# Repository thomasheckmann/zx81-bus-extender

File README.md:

# zx81-bus-extender v1
ZX81 Expansion port extender with power LED. Simple :-)

KiCad 8 files availble, in case you want to play around with it yourself - or Gerber files for producing PCBs.

BOM for v1:
- [ ] 2 x Edge Connector for ZX81

-- And optional

- [ ] LED any color, SMD
- [ ] 1K Ohm resistor, SMD
- [ ] 100 nF capacitor, SMD

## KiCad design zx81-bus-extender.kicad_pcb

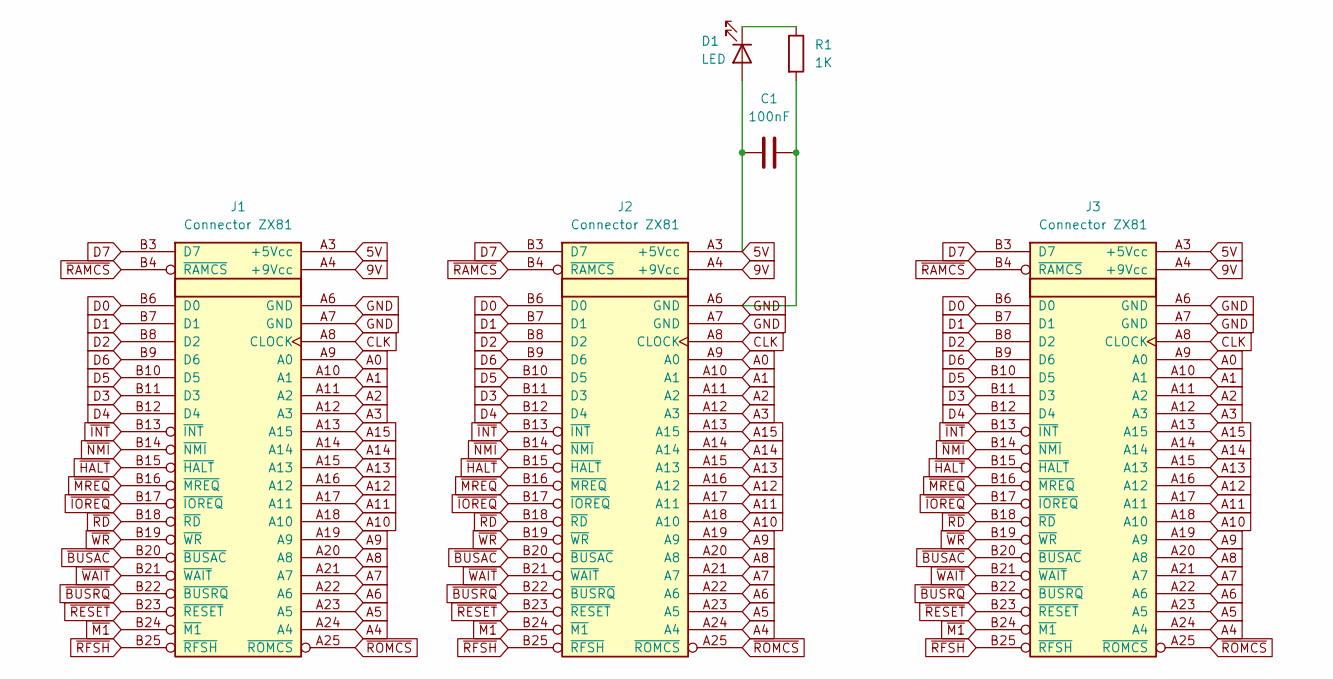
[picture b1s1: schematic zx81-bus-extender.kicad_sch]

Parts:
C1: 100nF; C_1206_3216Metric_Pad1.33x1.80mm_HandSolder
D1: LED; LED_1206_3216Metric_Pad1.42x1.75mm_HandSolder
J1: Connector ZX81; EDGE ZX81 BOTTOM
J2: Connector ZX81; EDGE ZX81 90
J3: Connector ZX81; EDGE ZX81 TOP
R1: 1K; R_1206_3216Metric_Pad1.30x1.75mm_HandSolder

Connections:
5V: C1.1, D1.2 (A), J1.A3 (+5Vcc), J2.A3 (+5Vcc), J3.A3 (+5Vcc)
9V: J1.A4 (+9Vcc), J2.A4 (+9Vcc), J3.A4 (+9Vcc)
A0: J1.A9 (A0), J2.A9 (A0), J3.A9 (A0)
A1: J1.A10 (A1), J2.A10 (A1), J3.A10 (A1)
A2: J1.A11 (A2), J2.A11 (A2), J3.A11 (A2)
A3: J1.A12 (A3), J2.A12 (A3), J3.A12 (A3)
A4: J1.A24 (A4), J2.A24 (A4), J3.A24 (A4)
A5: J1.A23 (A5), J2.A23 (A5), J3.A23 (A5)
A6: J1.A22 (A6), J2.A22 (A6), J3.A22 (A6)
A7: J1.A21 (A7), J2.A21 (A7), J3.A21 (A7)
A8: J1.A20 (A8), J2.A20 (A8), J3.A20 (A8)
A9: J1.A19 (A9), J2.A19 (A9), J3.A19 (A9)
A10: J1.A18 (A10), J2.A18 (A10), J3.A18 (A10)
A11: J1.A17 (A11), J2.A17 (A11), J3.A17 (A11)
A12: J1.A16 (A12), J2.A16 (A12), J3.A16 (A12)
A13: J1.A15 (A13), J2.A15 (A13), J3.A15 (A13)
A14: J1.A14, J2.A14, J3.A14
A15: J1.A13 (A15), J2.A13 (A15), J3.A13 (A15)
CLK: J1.A8 (CLOCK), J2.A8 (CLOCK), J3.A8 (CLOCK)
D0: J1.B6 (D0), J2.B6 (D0), J3.B6 (D0)
D1: J1.B7 (D1), J2.B7 (D1), J3.B7 (D1)
D2: J1.B8 (D2), J2.B8 (D2), J3.B8 (D2)
D3: J1.B11 (D3), J2.B11 (D3), J3.B11 (D3)
D4: J1.B12 (D4), J2.B12 (D4), J3.B12 (D4)
D5: J1.B10 (D5), J2.B10 (D5), J3.B10 (D5)
D6: J1.B9 (D6), J2.B9 (D6), J3.B9 (D6)
D7: J1.B3 (D7), J2.B3 (D7), J3.B3 (D7)
GND: C1.2, J1.A6 (GND), J1.A7 (GND), J2.A6 (GND), J2.A7 (GND), J3.A6 (GND), J3.A7 (GND), R1.2
unnamed: D1.1 (K), R1.1
~BUSAC: J1.B20 (~BUSAC), J2.B20 (~BUSAC), J3.B20 (~BUSAC)
~BUSRQ: J1.B22 (~BUSRQ), J2.B22 (~BUSRQ), J3.B22 (~BUSRQ)
~HALT: J1.B15 (~HALT), J2.B15 (~HALT), J3.B15 (~HALT)
~INT: J1.B13 (~INT), J2.B13 (~INT), J3.B13 (~INT)
~IOREQ: J1.B17 (~IOREQ), J2.B17 (~IOREQ), J3.B17 (~IOREQ)
~M1: J1.B24 (~M1), J2.B24 (~M1), J3.B24 (~M1)
~MREQ: J1.B16 (~MREQ), J2.B16 (~MREQ), J3.B16 (~MREQ)
~NMI: J1.B14 (~NMI), J2.B14 (~NMI), J3.B14 (~NMI)
~RAMCS: J1.B4 (~RAMCS), J2.B4 (~RAMCS), J3.B4 (~RAMCS)
~RD: J1.B18 (~RD), J2.B18 (~RD), J3.B18 (~RD)
~RESET: J1.B23 (~RESET), J2.B23 (~RESET), J3.B23 (~RESET)
~RFSH: J1.B25 (~RFSH), J2.B25 (~RFSH), J3.B25 (~RFSH)
~ROMCS: J1.A25 (~ROMCS), J2.A25 (~ROMCS), J3.A25 (~ROMCS)
~WAIT: J1.B21 (~WAIT), J2.B21 (~WAIT), J3.B21 (~WAIT)
~WR: J1.B19 (~WR), J2.B19 (~WR), J3.B19 (~WR)

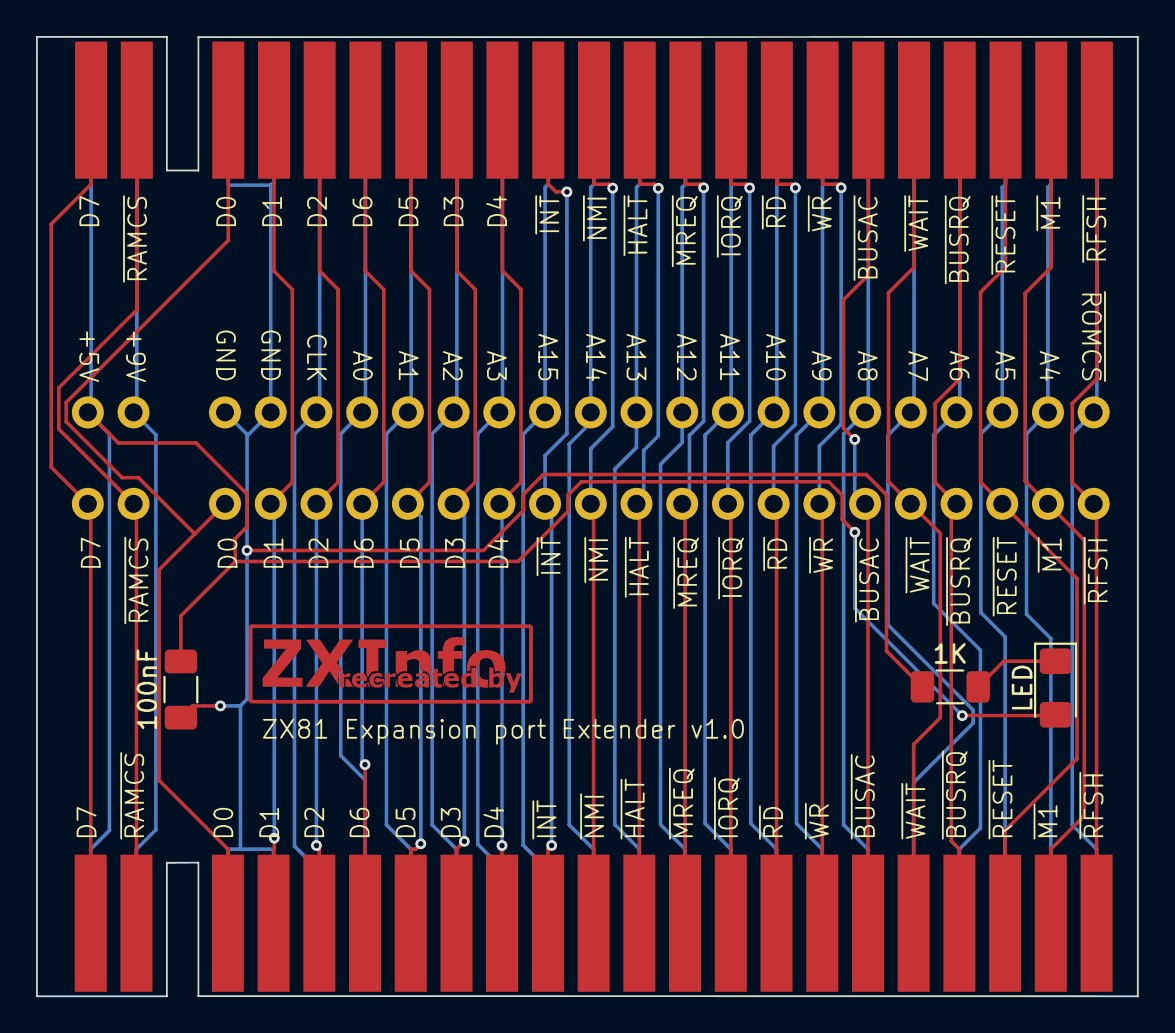
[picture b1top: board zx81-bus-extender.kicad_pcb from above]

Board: 2 copper layers, 61.2 x 53.3 mm, 7 parts (0 on the bottom side), 44 nets.

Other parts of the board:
G200: LOGO; ZXInfo_kicad_logo_copper_16.5x5

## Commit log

2024-04-15 Initial v1.0.0
